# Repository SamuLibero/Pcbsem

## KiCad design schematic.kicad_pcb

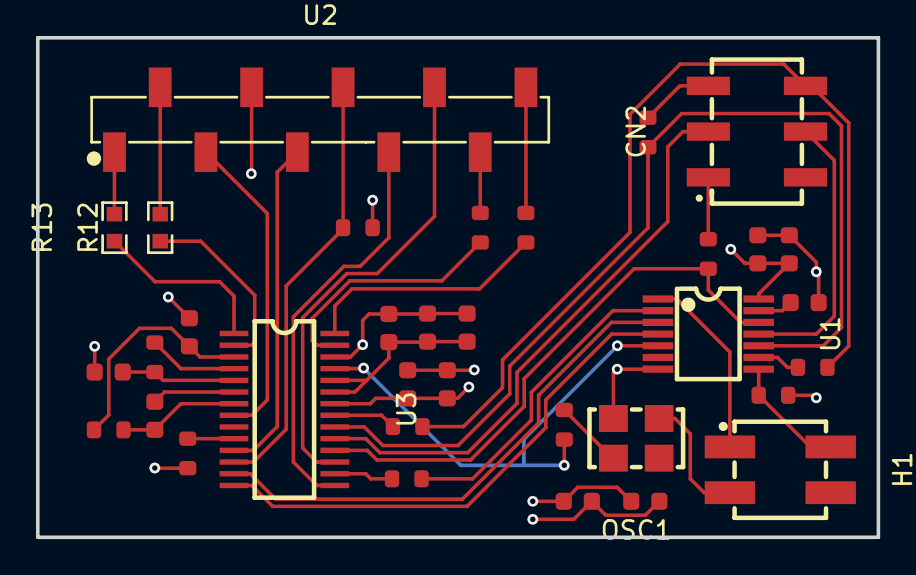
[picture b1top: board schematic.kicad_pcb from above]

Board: 4 copper layers, 46.7 x 27.8 mm, 34 parts (0 on the bottom side), 40 nets.

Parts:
C1, C7, C11, C12: 100nF; C_0603
C2, C5, C9, C10, C13: 10nF; C_0603
C3: 2.7nF; C_0603
C4: 1.5nF; C_0603
C6: 1uF; C_0603
C8: 10uF; C_0603
CN2: PM254-2-03-S-8.5; HDR-SMD_6P-P2.54-V-F-R2-C3-LS7.0
H1: X6521WVS-2*02H-C60D74; HDR-SMD_4P-P2.54-V-M-R2-C5-S7.4
OSC1: OT1EL89CJI-111YLC-16M; OSC-SMD_4P-L5.0-W3.2-BL_7CZ-XXXXX
R1, R5, R6, R7, R11, R17: 33Ω; R_0603
R2, R16: 10Ω; R_0603
R3: 1.1kΩ; R_0603
R4: 510Ω; R_0603
R10, R14: 10kΩ; R_0603
R12, R13: 0603WAF9100T5E; R0603
R15: 5.1kΩ; R_0603
U1: TDC7200PWR; TSSOP-14_L5.0-W4.4-P0.65-LS6.4-BL
U2: X6511WVS-10H-C60D48R2; HDR-SMD_10P-P2.54-V-M-LS4.8_R2
U3: TDC1000PWR; TSSOP-28_L9.8-W6.6-P0.65-BL

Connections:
/3.3V: C1.2, C2.2, C7.2, C8.2, C9.2, C10.2, C11.2, C12.2, C13.2, OSC1.4 (VDD), R10.2, R14.2, U1.14 (VDD), U3.22 (VIO), U3.23 (VDD), U3.24 (VDD)
/CHSEL_TDC1000: U2.5, U3.11 (CHSEL)
/CHSEL_TDC7200: CN2.5, U1.11 (CSB)
/CLOCK: R17.2, U1.5 (CLOCK), U3.25 (CLKIN)
/CSB_TDC1000: CN2.2, U3.19 (CSB)
/ENABLE_TDC1000: U2.7, U3.15 (EN)
/ENABLE_TDC7200: H1.1, U1.1 (ENABLE)
/EN_OSC: H1.3, OSC1.1 (Tri-state)
/ERRB_TDC1000: R14.1, U2.6, U3.12 (ERRB)
/GND: C1.1, C2.1, C3.2, C5.1, C6.2, C7.1, C8.1, C9.1, C10.1, C11.1, C12.1, C13.1, OSC1.2 (GND), R4.2, U1.7 (GND), U2.4, U3.26 (GND)
/INTB_TDC7200: H1.2, R10.1, U1.8 (INTB)
/MISO: CN2.4, R1.2, R5.1
/MOSI: R6.1, U1.10 (DIN), U3.20 (SDI)
/RESET_TDC1000: U2.8, U3.17 (RESET)
/RTD1: U2.3, U3.8 (RTD1)
/RX1: R13.2, U2.1
/RX2: R12.2, U2.2
/SCLK: R7.1, U1.12 (SCLK), U3.18 (SCLK)
/START: U1.3 (START), U3.13 (START)
/STOP: U1.4 (STOP), U3.14 (STOP)
/TRIGGER: R11.1, U3.16 (TRIGGER)
/TX1: R16.1, U2.10
/TX2: R2.1, U2.9
unnamed: CN2.1, R7.2
unnamed: CN2.3, R6.2
unnamed: OSC1.3 (OUT), R17.1
unnamed: R1.1, U1.9 (DOUT)
unnamed: R11.2, U1.2 (TRIGG)
unnamed: C6.1, U1.13 (VREG)
unnamed: C4.2, R15.2, U3.7 (COMPIN)
unnamed: R3.1, U3.4 (LNAOUT)
unnamed: C3.1, R3.2, U3.5 (PGAIN)
unnamed: C4.1, U3.6 (PGAOUT)
unnamed: R4.1, U3.10 (RREF)
unnamed: R13.1, U3.1 (RX1)
unnamed: R12.1, U3.2 (RX2)
unnamed: R5.2, U3.21 (SDO)
unnamed: R16.2, U3.28 (TX1)
unnamed: R2.2, U3.27 (TX2)
unnamed: C5.2, R15.1, U3.3 (VCOM)
